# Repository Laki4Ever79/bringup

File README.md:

# Bringup

**Change “one thing”, and the whole hardware design follows: board, case, firmware and parts, in parallel.**

**▶ Watch the 3-minute demo: [youtu.be/b0B6R5KyZ64](https://youtu.be/b0B6R5KyZ64)**

<sub>Recorded run, scripted agents with the real tools (tscircuit + KiCad, build123d, PlatformIO). The waiting is cut: the
ripple took 3 min 15 s.</sub>

A short product brief goes in. Concurrent [Mozaik](https://www.npmjs.com/package/@mozaik-ai/core) agents turn it into
parts with JLCPCB order numbers, a routed PCB, a printable case whose cutouts match the board, and firmware that
compiles against the real pin map. Then the design changes, the way real designs always do, and Bringup keeps every
part of it consistent. Even designing from scratch is just the first change: the beacon's first design took 7 contract
revisions.

Bringup is a demonstrator for one product family: ESP32-C3 boards built from a small, vetted parts catalog.
3ALET Hackathon 2026, Freestyle track. Built on `@mozaik-ai/core` 4.1.0. Full details: [docs/details.md](docs/details.md).

**The fastest way to see it: [bringup-demo.onrender.com](https://bringup-demo.onrender.com/)**, nothing to install. A read-only dashboard of recorded
runs (the first load after idle takes about 30 s), or press **Try it**: a stubbed scripted run you can change once
("add a temperature/humidity sensor"). The recorded runs used the real tools; live runs there are stubbed, because
the real toolchain (KiCad in Docker, the ESP32 compiler, about 9.6 GB and minutes of full CPU per build) doesn't fit a
free web host. [Why, in detail](docs/details.md#why-the-live-demo-is-stubbed).

## What's real, what's scripted

| Part | In the quick look | In the recorded runs (`docs/runs/`) | On the live site | Locally, fully installed |
|---|---|---|---|---|
| Agents | scripted | scripted (most) · real models (`real-*`, `add-sensor-real*`) | scripted | scripted or real models (your key in `.env`) |
| Board, case, firmware builds | stubbed | real tools | real tools (recorded) · stubbed (Try it) | real tools |
| Checks (consistency, grounding) | real | real | real | real |
| Final brief review | scripted | scripted or a real model | scripted | scripted or a real model |
| The ESP32 board | none | bench runs only | none | `--bench real` |

## Quick look (Node 24 only, no API key, about 1 min)

```bash
git clone https://github.com/Laki4Ever79/bringup && cd bringup && npm ci
npm run bringup -- briefs/logger.md --mock --no-hardware --out out/quick
cat out/quick/report.md   # "settled ... Violations: 0", plus the change requests held by interception
```

This quick look stubs the hardware tools, so it builds no board or case. To see what the real tools produce without
installing them, open the recorded run [docs/runs/add-sensor/](docs/runs/add-sensor/): the
[board render](docs/runs/add-sensor/board/rev-10/board.png), the printable [case](docs/runs/add-sensor/enclosure/rev-9/case.stl)
and [lid](docs/runs/add-sensor/enclosure/rev-9/lid.stl) (GitHub shows them in 3D), the
[report](docs/runs/add-sensor/report.md) and the full trace.

**Words used below.** *Contract*: the one shared design every agent reads and writes. *Settled*: every built file
matches the contract and nothing is left to do. *Grounding*: checking every part and pin against the parts catalog and
KiCad's symbol library. *Brief reviewer*: an AI that judges the finished design against the original brief, with none
of the agents' history.

## What it does

### 1. A brief becomes a whole design

Nine participants, each its own Mozaik loop, work at the same time against **one live design contract**: parts with
LCSC numbers, a routed KiCad board, a printable case and lid, and firmware for the real pin map, booted in QEMU.

### 2. Change one thing, and only what it affects wakes up

"Add a temperature/humidity sensor": the parts agent added the SHT40, the architect wired it, the board re-routed, the
firmware switched on its driver, and **the case cut a vent over the sensor**. 7 of 9 agents woke, 9 mismatches were
caught live, and the design was consistent again in 195 s (`docs/runs/add-sensor/`, scripted agents, real tools).

### 3. Or just edit the files yourself

Save an edited `pins.h` or the board in KiCad, and the save becomes a change request: the rest of the design follows. A
linked folder is a git repo with one commit per settled revision; an edit the contract can't hold is flagged, never
silently overwritten (`docs/runs/file-sync/`, `docs/runs/linked/`).

### 4. All the way to a real board, and ready to order

"Blink faster when tilted" changed only the firmware; the real board was reflashed in 16 s and, tilted, blinked at
**244 ms measured** against the 250 ms asked (an ESP32-S3 dev board standing in for the design's ESP32-C3). Every run
hands you case and lid STLs, a JLCPCB fab package and firmware; on a fully green run, **Ready to order** zips exactly
the files JLCPCB asks for and opens the quote page (nothing is uploaded or ordered).

### 5. An on-device model is one more domain that follows

"Add a wake word" asks only for a model. The checks carry it through the rest of the design:

- the parts add a microphone, and the board places it on the maker's land pattern
- the case gets an opening under the sound hole
- the firmware reserves the model's memory, so `pio` counts it
- power moves to USB, because always-on listening breaks the battery target

The model is tied to the sensor path its data was recorded on. A later change such as "make it 40 mm wide" moves the
microphone, and the ml agent marks the data as needing re-recording. Bringup also generates the data-collection
firmware, and checks a TFLite int8 model against the board (`bringup verify-model`). Details:
[docs/edge-ai.md](docs/edge-ai.md).

### 6. So does the production test

"Add a production test fixture" wakes a test agent, which owns the test: which nets get a test pad, and the current
a good board stays under. The board gets pogo pads on its underside, and a test kit is built beside it: a printable
bed-of-nails fixture, factory-test firmware and a test plan with pass limits. "Add a wake word" adds mic pins, and the
test agent gives them pads. "Make it 40 mm wide" moves the pads, and the fixture's holes move with them. Details:
[docs/test-kit.md](docs/test-kit.md).

On an existing KiCad repo, the `adopt` GitHub Action can now comment on a pull request with its change impact: what
the change moved, and which of board, case, firmware and BOM must follow, down to the firmware line
([docs/adopt.md](docs/adopt.md)). And a part out of stock gets options, not an automatic change: other suppliers first,
then a catalog drop-in with what switching would change.

### 7. Ask for the case you want

"Add wall-mount tabs", "engrave "BRINGUP" on the lid", "add a cable gland": a case designer agent owns the case's
walls, height and added features, and the case is rebuilt around the board with them. Each feature is measured on the
built solid. A case change that needs a different board ("make the case 50 mm wide" means a 37.1 mm board, since the
module's antenna hangs past the board's edge) never
happens silently: you get a warning that the PCB will change, and it goes ahead only if you approve it. Details:
[docs/case-editing.md](docs/case-editing.md).

Board and case are compact by default: code computes the smallest board the parts place on, and anything more than
15% over it needs a recorded reason (your size, usability, a standard fit, function, assembly and test, expansion, or
a measured routing failure). The report says what the size costs. A board that fails KiCad's DRC, or that the
router can't finish, wakes the architect to give it room. The ESP32-C3 module sits at the board edge opposite the
USB-C port, its antenna hanging past the edge as Espressif recommends; the case and the test fixture leave it room.
Rules and sources: [docs/space-rules.md](docs/space-rules.md).

### 8. And how it connects

"Show the readings in Home Assistant": the connectivity engineer adds BTHome to the Bluetooth broadcast, and Home
Assistant picks the device up with no app. "Send them over Wi-Fi every hour": the firmware switches to Wi-Fi and MQTT
with Home Assistant discovery. The checks then follow the radio: Wi-Fi's 350 mA transmit peak raises the rail, the
hourly uploads break the 180-day battery target until they're stretched, and field updates cost a second firmware
slot that a bigger model may not fit. Details: [docs/connectivity.md](docs/connectivity.md).

No case, or your own: "bare board, no case" builds and checks no case, and "it goes into our own housing" writes
`interface.md` (outline, mounting holes, openings, lights, vents, antenna keep-out, label) instead. What Bringup adds
without being asked (a case nobody mentioned, USB wake, recovery pads, a battery assumption) is listed in the report
under "Added for you", with how it shows and how to turn it off.

### 9. Several boards, one system

`npm run bringup -- system briefs/systems/logger-beacon-uart.json` designs each board in its own run, in parallel,
and joins them with UART or I2C links over a 4-pin JST SH cable. Each board gets one extra field, its side of each link;
its own agents add the connector and pins. Code then checks the boards against each other: TX meets RX through the
cable, matching speeds, one I2C controller, unique addresses, one set of pull-ups, the cable's length and voltage drop,
and one message definition on both sides. Out come the cable drawing, a WireViz file and a shared message header, and
each UART link's two firmwares are run together in QEMU over a virtual cable. Details: [docs/system.md](docs/system.md).

### 10. Any vendor's MCU, chosen on equal terms

Chip facts are data, not code: each MCU has a profile (`catalog/mcu/`) with its pins, the signals each pin can carry,
peripherals, reserved pins, support parts, currents, firmware target and simulator. STM32 profiles are generated from
ST's open pin data. The parts agent ranks every chip on the same terms (`compare_mcus`), a pin solver assigns pins and
peripheral instances the way CubeMX would, and the board, firmware, simulation and checks follow the chosen chip.
`npm run bringup -- briefs/logger-stm32.md --mock` runs the whole pipeline on an STM32G031: an LQFP board with its
decoupling, firmware from the same template, booted in Renode. ESP32-C3, STM32 (G0, L0, F1 with its crystal, WB55),
RP2040 and nRF52840 are profiled; what each can do today is in [docs/mcu.md](docs/mcu.md).

### 11. A part it doesn't know, it learns

When a plan needs a part the catalog lacks (a speaker, an amplifier), Bringup finds candidates at LCSC, DigiKey, Mouser
or the manufacturer, reads each datasheet with a model, and keeps a number only if it checks out: its value is in the
page's own words near where the model said, or two reads of an image-only drawing agree. Every number keeps its page and region;
a missing critical one (size, pin-out, supply limits, footprint, mount holes where the part has them) is never guessed, so the next candidate
is tried instead. Spending is capped per design run ($2 by default). The wiring of learned parts into the board and
firmware is the next step and is not built yet; see [docs/system.md](docs/system.md#part-learner).

## Architecture

```mermaid
flowchart LR
  E["Engineer<br/>brief · typed change · saved file"] -->|"change.requested"| C
  subgraph RS["Mozaik RuntimeState"]
    C[("Design contract<br/>fields with an owner and a version")]
  end
  A["architect (LLM)"] <--> C
  P["parts (LLM)"] <--> C
  C -->|"contract.changed<br/>situations decide who wakes"| B["board<br/>tscircuit + KiCad"]
  C --> X["case<br/>build123d"]
  C --> F["firmware<br/>PlatformIO + QEMU"]
  B --> K["consistency + grounding<br/>(plain code)"]
  X --> K
  F --> K
  K -->|"violations wake the owners"| A
  K -->|"design.ready"| R["brief reviewer<br/>(LLM, fresh context)"]
  R -->|"findings to the field owners"| A
  A -.->|"a change to a field it does not own"| I{{"interception:<br/>held for the owner"}}
```

There is no orchestrator: no agent calls or awaits another. How it uses Mozaik:

- **`RuntimeState`** holds one live design contract per run; every field has an owner and a version.
- **Situations are the dependency graph**: each participant's situations decide which changes wake it.
- **`runLoop`** is fire-and-forget, so every agent turn runs concurrently with the others.
- **`InterceptionHandler` is change control**: a change to another owner's field is held mid-loop until the owner decides,
  and owners do say no: in real run 7 interception held 18 changes and the owners rejected 8 ([docs/runs/real-7](docs/runs/real-7/report.md)).
- **Plain-code participants** (builders and checks) and a custom `InferenceRunner` (`--mock` runs with no key).

Events, checks, the full Mozaik table and our 4.1 workarounds (#113, #114, #115) are in [docs/details.md](docs/details.md).

## Install & run

```bash
npm ci              # about 12 s
npm run setup       # the full toolchain, repo-local; installs only what's missing (about 14 min the first time)
npm run doctor      # what each tool will use, and which optional settings are set (never their values)
npm run demo        # the dashboard opens, a design settles, a change ripples; type your own change after it
npm run dashboard   # the start screen: describe a device, see the split into boards, build it, explore it in 3D
npm run perf        # the dashboard's speed budget, measured in a visible Chromium (no model calls)

npm run bringup -- briefs/beacon.md --mock                                    # scripted models, real tools
npm run bringup -- briefs/logger.md --mock --change "make the board 40 mm wide"   # a change from the CLI
npm run bringup -- briefs/rover.md --mock                                     # a robot: mechanics, chassis, simulated drive (docs/mechanics.md)
npm run bringup -- briefs/logger.md                                           # real models: a key in .env
```

Prerequisites: Linux x86-64, Node 24, [uv](https://docs.astral.sh/uv/), and Docker usable without `sudo`; about 9.6 GB
of disk. `npm run setup` checks them first and says plainly what's missing. Optional settings go in `.env` (copy
`.env.example`). The manual install steps, every command (link, status, simulate, tournament, MCP), the run folder and
the tests are in [docs/details.md](docs/details.md).

## Honest status

- Scripted runs settle with 0 violations and take mid-run changes, with the real board, case and firmware tools.
- Real models take mid-run changes too (run 20: a sensor swap rippled to consistent in 75 s, 40 mm wide in 28 s;
  that run as a whole then failed the final review and did not settle).
- **A real-model run has passed the final brief review.** We used the night's real-model runs to find and fix general problems (the designers now see the same computed facts as the reviewer, and the review's computable checks run live during design). After those fixes, run real-pass ([docs/runs/real-pass](docs/runs/real-pass/)) designed the beacon from its brief with real models and real tools, failed review 1, fixed itself and passed review 2 (settled at rev 19, 0 violations, about 8 minutes). Each real run tonight surfaced a concrete blocker, and each fix removed it for every run after it; that is how this run got through. A few known blockers remain (a lower-dropout regulator for the parts catalog, a longer advertising window, clearer battery assumptions), and each one removed should raise the pass rate further.
- Boards need a human review before ordering (`fab/README.txt` lists every item); the parts catalog is small.

## Credits

Prior art we credit: Odem, MeshCue Forge, Copperhead, DRCY, Engineering Studio AI; tscircuit and KiCad do the real EDA
work. What Bringup adds is change propagation across board, case, firmware and parts (details and links in
[docs/details.md](docs/details.md#prior-art-and-whats-new)).

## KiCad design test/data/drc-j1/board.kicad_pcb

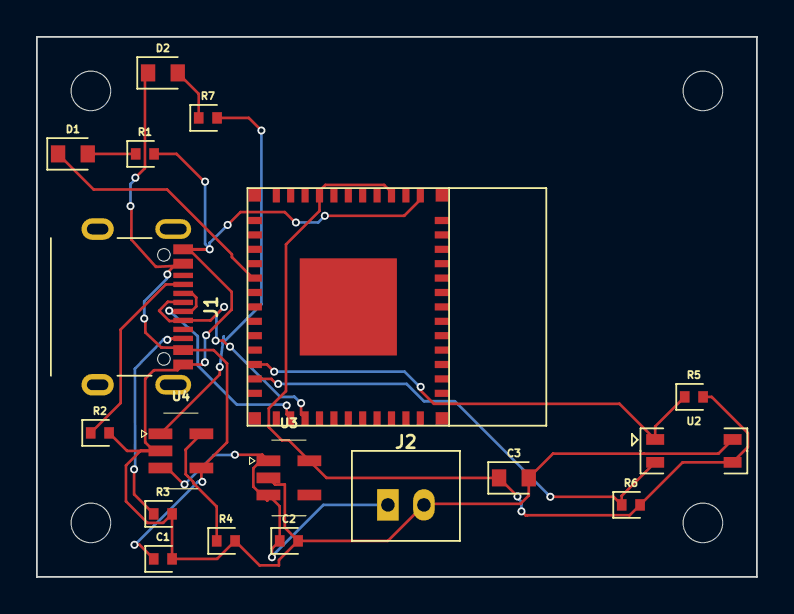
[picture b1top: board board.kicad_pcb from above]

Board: 2 copper layers, 40.0 x 30.0 mm, 18 parts (0 on the bottom side), 15 nets.

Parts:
C1, C2: chip_0402
C3: chip_0603
D1, D2: chip_0603
J1: J1; connector_usbcmidmount
J2: chip_jst2_ph
R1, R2, R3, R4, R5, R6, R7: chip_0402
U1: chip
U2: chip_dfn4
U3, U4: chip_sot23_5

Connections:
.D1 > .K to .R1 > .pin1: D1.2, R1.1
.D2 > .K to .R7 > .pin1: D2.2, R7.1
.J1 > .pin8 to .R2 > .pin1: J1.8, R2.1
.J1 > .pin14 to .R3 > .pin1: J1.14, R3.1
.U4 > .CHRG to .R7 > .pin2: R7.2, U4.1
.U4 > .PROG to .R4 > .pin1: R4.1, U4.5
GND: C1.2, C2.2, C3.2, J1.5, J1.16, J2.2, R1.2, R2.2, R3.2, R4.2, U1.1, U2.4, U3.2, U4.2
I2C_SCL: R6.1, U1.23, U2.2
I2C_SDA: R5.1, U1.22, U2.1
STATUS_LED: D1.1, U1.16
USB_DN: J1.9, J1.11, U1.26
USB_DP: J1.10, J1.12, U1.27
V3V3: C3.1, R5.2, R6.2, U1.3, U1.8, U2.3, U3.5
VBAT: C2.1, J2.1, U3.1, U3.3, U4.3
VBUS: C1.1, D2.1, J1.6, J1.15, U4.4

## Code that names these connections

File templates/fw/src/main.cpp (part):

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#endif
#endif

#if defined(PIN_I2C_SDA) && defined(PIN_I2C_SCL)
static_assert(HAL_PIN_VALID(PIN_I2C_SDA), "PIN_I2C_SDA is not a GPIO on this chip");
static_assert(HAL_PIN_VALID(PIN_I2C_SCL), "PIN_I2C_SCL is not a GPIO on this chip");
#define HAS_I2C 1
// The sensor is the only I2C part the product firmware drives: a design with no I2C pins has no sensor (briefs/beacon.md).
#define HAS_SENSOR 1
#endif

#ifdef PIN_STATUS_LED
static_assert(HAL_PIN_VALID(PIN_STATUS_LED), "PIN_STATUS_LED is not a GPIO on this chip");
#define HAS_LED 1
#endif

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// The LED's anode is on the GPIO and its cathode goes to GND through a resistor, so HIGH is on.
static void led(bool on) {
#ifdef HAS_LED
	digitalWrite(PIN_STATUS_LED, on ? HIGH : LOW);
#endif
}

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	bool duty = digitalRead(BENCH_MODE_PIN) == HIGH;
	if (esp_reset_reason() != ESP_RST_DEEPSLEEP) dutyCycles = 0;
#ifdef HAS_I2C
	Wire.begin(PIN_I2C_SDA, PIN_I2C_SCL);
#endif
#ifdef HAS_LED
	pinMode(PIN_STATUS_LED, OUTPUT);
#endif
	bootLine(duty);
	if (duty) dutyCycle();
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	for (;;) delay(1000);
#endif
#ifdef HAS_LED
	pinMode(PIN_STATUS_LED, OUTPUT);
#endif
#if defined(PIN_BUTTON) && defined(RADIO_BLE)
	// Woken by the button (not the timer, nor USB on the sense pin): stay visible long enough for a phone to connect.
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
